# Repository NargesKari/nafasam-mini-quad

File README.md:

# nafasam-mini-quad

A phone-to-ESP32 wireless control link for a quadcopter, built around a hand-specified binary protocol with a checksum, a kill switch, and a failsafe — the network layer a drone project needs before the flight controller is worth writing.

## What it does

- Runs the ESP32 as an open WiFi access point (`nafasm`) serving a touch-control web page straight from flash, so any phone can connect with no app install.
- The page has two virtual joysticks (left: throttle/yaw, right: pitch/roll), an ARM/DISARM button, status lights (link / IMU / armed) and a help panel. It polls `GET /control` every 100 ms.
- A 200 Hz FreeRTOS task on core 0 reads the MPU6050 directly over its registers (no library), estimates roll/pitch with a complementary filter, runs PID stabilisation, mixes for an X-configuration quad and drives four transistor-switched brushed motors with PWM.
- Safety: failsafe disarm after 500 ms of silence, arm refused with throttle up, motors off on any IMU error, crash-angle disarm.

See `docs/protocol.md` for the exact contract.

## Repo layout

- `firmware/nafasam_quad/` - Arduino sketch (`.ino`, `config.h` pins/PID/safety, `mpu6050.*` driver, generated `web_page.h`)
- `web/public/index.html` - control page (single source of truth)
- `hardware/` - schematics, PCB, datasheets, mechanical parts
- `docs/` - protocol
- `scripts/generate_web_header.py` - embeds the page into the firmware

## Getting started

Arduino IDE with the ESP32 core v3.x (no extra libraries), open `firmware/nafasam_quad/nafasam_quad.ino`, select an ESP32 Dev Module, upload. Power the drone flat and still: the gyro calibrates at boot.

If you edit the control page:

```bash
python3 scripts/generate_web_header.py   # then re-flash
```

Connect to the `nafasm` WiFi and open `http://192.168.4.1/`.

**First power-up: remove the propellers** and check each motor's direction and the sign of the stabilisation on the bench before any flight.

<!-- add screenshot/demo here -->

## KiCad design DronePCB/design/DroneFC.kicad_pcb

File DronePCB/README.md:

# DroneFC — engineering prototype A0

Open **design/DroneFC.kicad_pro** in KiCad 10. The project includes an editable seven-page schematic, a four-layer PCB, and local symbol/footprint libraries. The local libraries make the project portable.

**This is a prototype design, not a flight-tested or production-qualified controller. Read reports/validation-summary.json for the latest checks. Do not fabricate from an intermediate routing file.**

## Design choices

- ESP32-S3-MINI-1-N4R2: soldered module with 4 MB flash and 2 MB PSRAM. The module integrates RF circuitry and a PCB antenna. A bare ESP32 silicon implementation would require additional RF, clock and memory design.
- MPU-6050 bare QFN chip, I2C address 0x68. The auxiliary sensor bus and reserved pins are intentionally unused.
- Four AO3400A low-side motor switches, four SS34 flyback diodes, 100-ohm gate resistors, and 10-kilohm gate-to-source pulldowns.
- One 700 mAh, 20C, 1S LiPo. The advertised continuous discharge calculation is 0.7 Ah × 20 = 14 A; it does not establish the battery's real internal resistance or transient capability.
- TPS63021 fixed 3.3 V buck-boost converter for electronics, with a 1.5 uH inductor, two 10 uF input capacitors, three 22 uF output capacitors, and 100 nF control-supply bypass. Target electronics load is up to 1 A at battery voltage ≥3.0 V, subject to thermal/transient testing.
- TLV70028 and TLV70012 regulators provide the camera's 2.8 V and 1.2 V rails.
- A 10-ohm/1 uF filter feeds the IMU; local VDD, VLOGIC, REGOUT and CPOUT capacitors are 100 nF, 10 nF, 100 nF and 2.2 nF respectively. CPOUT uses a 50 V-rated capacitor.
- No charging circuit, SD card slot, USB socket, development-board headers, or flash LED. Programming uses solder pads and an external 3.3 V UART adapter.

## Mechanical and stackup intent

PCB outline: **50 × 50 mm**, nominal **0.8 mm** FR4, four copper layers. This is the first layout size, not a claim of minimum achievable size or mass. The antenna end of the ESP32 module extends beyond the PCB outline, so the assembled envelope is larger than 50 mm in that direction.

Layers: front signals/components, inner ground, inner battery distribution, back signals. Two camera signals (PCLK and RESET) also use the battery layer with clearance around them; the ground plane remains continuous. Ground and battery use solid connections to the inner planes. The motor-current pads use multiple vias. The final copper thickness, stackup, minimum spacing and via process must be agreed with the board manufacturer. The thermal/current assumptions require approximately 35 um finished copper on the power planes and outer layers; do not silently substitute thinner inner copper.

U2 uses the local TI_DSJ14_TPS63021 footprint, with a 1.58 × 2.85 mm exposed ground pad checked against TI drawing 4208549-3/E. Its peripheral lands are slightly enlarged relative to TI's example. Segmented paste covers approximately 65% of the exposed pad. Have the assembler qualify stencil thickness and via-in-pad treatment, including the module ground pads and the regulator ground connection. This is not a qualified assembly process.

Four M2 clearance holes use a nominal 44 × 26 mm spacing. Confirm that this pattern fits the frame. Keep the module antenna free of battery, carbon fibre, motors and wiring. The PCB is a controller mounted to a frame, not a structural motor-support plate.

## Camera compatibility

J3 uses **Hirose FH12-24S-0.5SH(55)**, a 24-pin, 0.5 mm pitch, bottom-contact FPC connector. Its electrical pinout follows the OV2640 interface shown in the AI-Thinker ESP32-CAM v1.6 reference schematic archived in references/ESP32_CAM_V1.6.pdf.

Buy only a camera flex assembly with this exact pinout. “OV2640” alone does not specify the connector pinout, contact side, flex thickness, lens clearance or power rails. The final camera assembly has not been selected from a seller. **The seller's flex drawing must be checked before fabrication.** The provided connector is not a generic plug for every ESP32 camera.

The camera's Y2–Y9 lines form D0–D7. Y0/Y1 and pin24 are unused. Camera I/O runs at 3.3 V, analog at 2.8 V and core at 1.2 V, consistent with the referenced assembly. See pin-map.json for the exact connections.

## Motor and battery connections

J2 pin1 is battery positive, pin2 is ground. J4–J7 pin1 is motor positive (VBAT), pin2 is the switched motor negative. SS34 cathodes connect to VBAT and anodes to motor negative. AO3400A pin1 is gate, pin2 source, pin3 drain.

**C101–C104 are off-board components:** solder one 100 nF, 16 V ceramic directly across each motor's terminals. Their presence in the BOM is intentional; they have no PCB footprints. C25–C28 are separate local 10 uF rail-decoupling capacitors near the motor drivers. C11 is a low-ESR 220 uF bulk capacitor. Its exact manufacturer part number, ripple rating, ESR and height remain a sourcing check; its allocated package is 6.3 × 5.8 mm.

The linked ECA listing describes 1.74 A as maximum loaded current. Four motors at that figure draw 6.96 A, excluding electronics. Stall/startup current is not specified by that figure. Measure it with current limiting and appropriate test equipment. Do not infer MOSFET, diode or battery stall survival from their headline current ratings.

AO3400A's specified 48 milliohm maximum at 2.5 V gate drive gives approximately 0.145 W conduction loss per motor at 1.74 A and continuous on-time at the datasheet reference temperature. Hot resistance, switching loss and flyback-diode dissipation increase the actual thermal load. This calculation is not a thermal qualification.

There is no reverse-polarity protection, battery charger or hardware LiPo cutoff on this board. Confirm polarity before connection, use an external 1S charger, and disconnect the battery after use. Battery voltage monitoring is available to firmware through a 100k/100k divider and 100 nF filter. The nominal ADC scale factor is 2, with calibration still required.

## Programming and firmware requirements

J1 pads, in order: GND, 3V3, UART_TX, UART_RX, BOOT, ESP_EN. Use **3.3 V logic**. Connect adapter TX to board RX and adapter RX to board TX. With the battery powering the board, use J1's 3V3 as a reference only; do not connect a second driven supply. Hold BOOT low while pulsing ESP_EN low to enter the ROM loader.

The included firmware header only defines hardware pins. It is not flight-control firmware. Before flying, implement and test local IMU sampling, calibration, attitude estimation, motor mixing, arming, link-loss response, watchdog response and low-battery handling. Flight stabilization must run locally; Wi-Fi carries commands/video rather than providing the timing of the stabilization loop. Keep camera processing from delaying the control loop.

All motor PWM outputs must initialize low. Establish a measured control-loop budget with camera streaming enabled. A fresh 1S cell reaches 4.2 V; the motors are listed as nominal 3.7 V. Confirm their permitted supply and use a battery-aware duty limit as appropriate. An average-voltage duty limit does not limit instantaneous stall current.

## Bench acceptance before flight

1. Inspect soldering and check supply resistance and polarity without battery connected. Start on a current-limited supply with motors disconnected.
2. Sweep battery input over the intended operating range and verify 3.3 V, 2.8 V, 1.2 V and IMU supply voltage, including camera/Wi-Fi transients.
3. Read MPU-6050 identity, check stationary gyro/accelerometer readings and confirm axis orientation. Check camera frames and the UART boot process.
4. With propellers removed, verify each motor remains off at boot/reset and test PWM individually. Then use a restrained thrust test to establish propeller load, startup current, voltage sag and component temperature.
5. Verify arming, loss-of-link response, watchdog reset and low-battery behavior before any flight. Establish thrust margin using the actual all-up mass.

## Sources

- [ESP32-S3-MINI module datasheet](https://documentation.espressif.com/esp32-s3-mini-1_mini-1u_datasheet_en.html)
- [Espressif camera driver and supported sensors](https://github.com/espressif/esp32-camera)
- [AI-Thinker ESP32-CAM v1.6 reference schematic, hosted by Seeed](https://github.com/SeeedDocument/forum_doc/blob/master/reg/ESP32_CAM_V1.6.pdf)
- [MPU-6000/6050 manufacturer specification](https://invensense.tdk.com/wp-content/uploads/2015/02/MPU-6000-Datasheet.pdf)
- [AO3400A manufacturer specifications](https://www.aosmd.com/products/mosfets/low-voltage-mosfets-12v-30v/ao3400a)
- [TPS63020/21 manufacturer datasheet](https://www.ti.com/lit/ds/symlink/tps63020.pdf)
- [XFL4020 inductor drawing](https://www.coilcraft.com/getmedia/50632d43-da1b-4cdb-8ab4-3029cab51df3/xfl4020.pdf)
- [Hirose camera connector](https://www.hirose.com/product/p/CL0586-0521-0-55)
- [ECA 8520 motor listing](https://eshop.eca.ir/موتور-coreless/6933-موتور-coreless-سایز-8520.html)

## Project contents

- design/DroneFC.kicad_pro, .kicad_sch and .kicad_pcb: editable KiCad project.
- BOM.csv: individual component values, packages and sourcing notes.
- design_manifest.json: component/net design intent; the PCB contains the final adjusted placement.
- pin-map.json and drone_pins.h: interface mapping.
- reports/: electrical, physical and connectivity checks.
- preview/: schematic and board previews.
- tools/ (working directory only, omitted from the delivery archive): development helpers and project-local routing tools. These contain intermediate design assumptions. Re-running build_design.py with --pcb replaces the board with its initial unrouted placement. Preserve the final PCB and local libraries before regenerating.

## Validation and delivery

The final routed PCB passes the configured KiCad electrical and physical checks with zero reported violations and zero unconnected items. An independent exported-netlist comparison matches all 240 connected component pins between schematic and PCB. The JSON reports list the checks that KiCad ignores under the project settings; a clean report does not establish thermal performance, signal integrity or flight suitability.

DroneFC-prototype-A0.zip contains the editable design, local libraries, component list, pin mapping, final reports and previews. No manufacturing release is included: camera flex compatibility, C11 sourcing, assembly process and manufacturer stackup still require confirmation. Actual motor startup/stall current, rail transients, thermal behavior and thrust margin require hardware tests. Board mass and efficiency have not been measured.

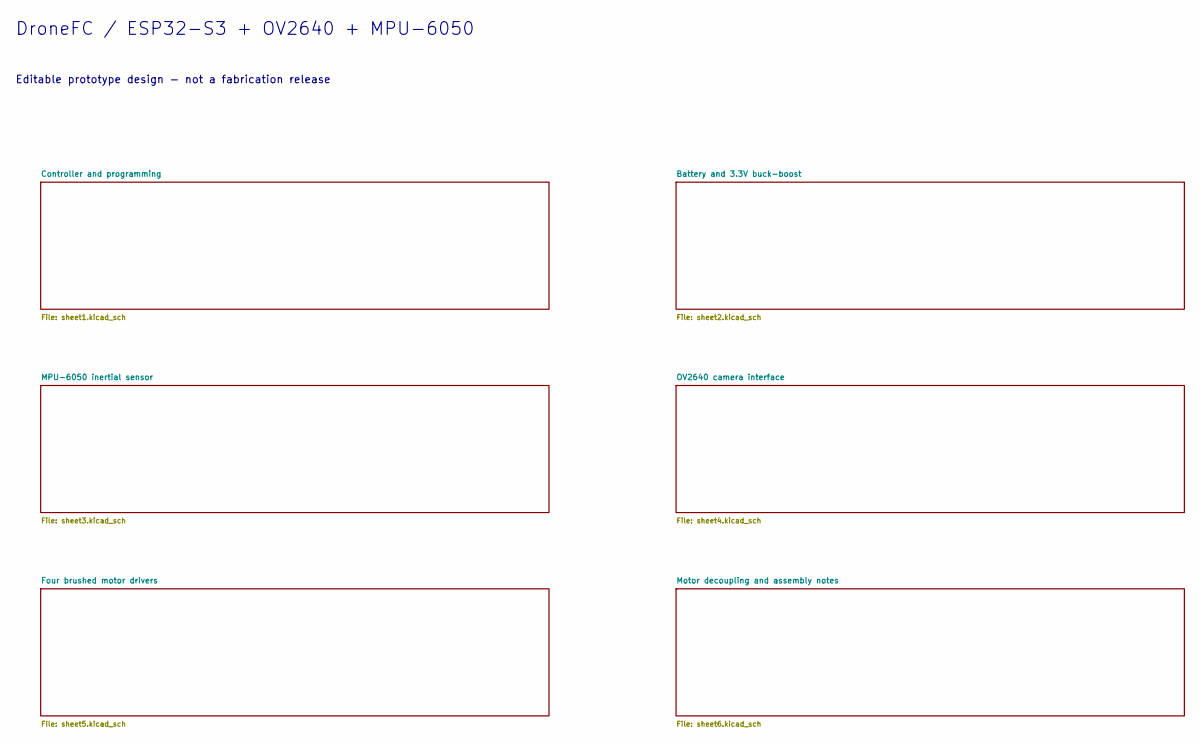
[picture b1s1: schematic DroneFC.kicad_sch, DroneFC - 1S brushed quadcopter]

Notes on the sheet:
DroneFC / ESP32-S3 + OV2640 + MPU-6050
Editable prototype design - not a fabrication release

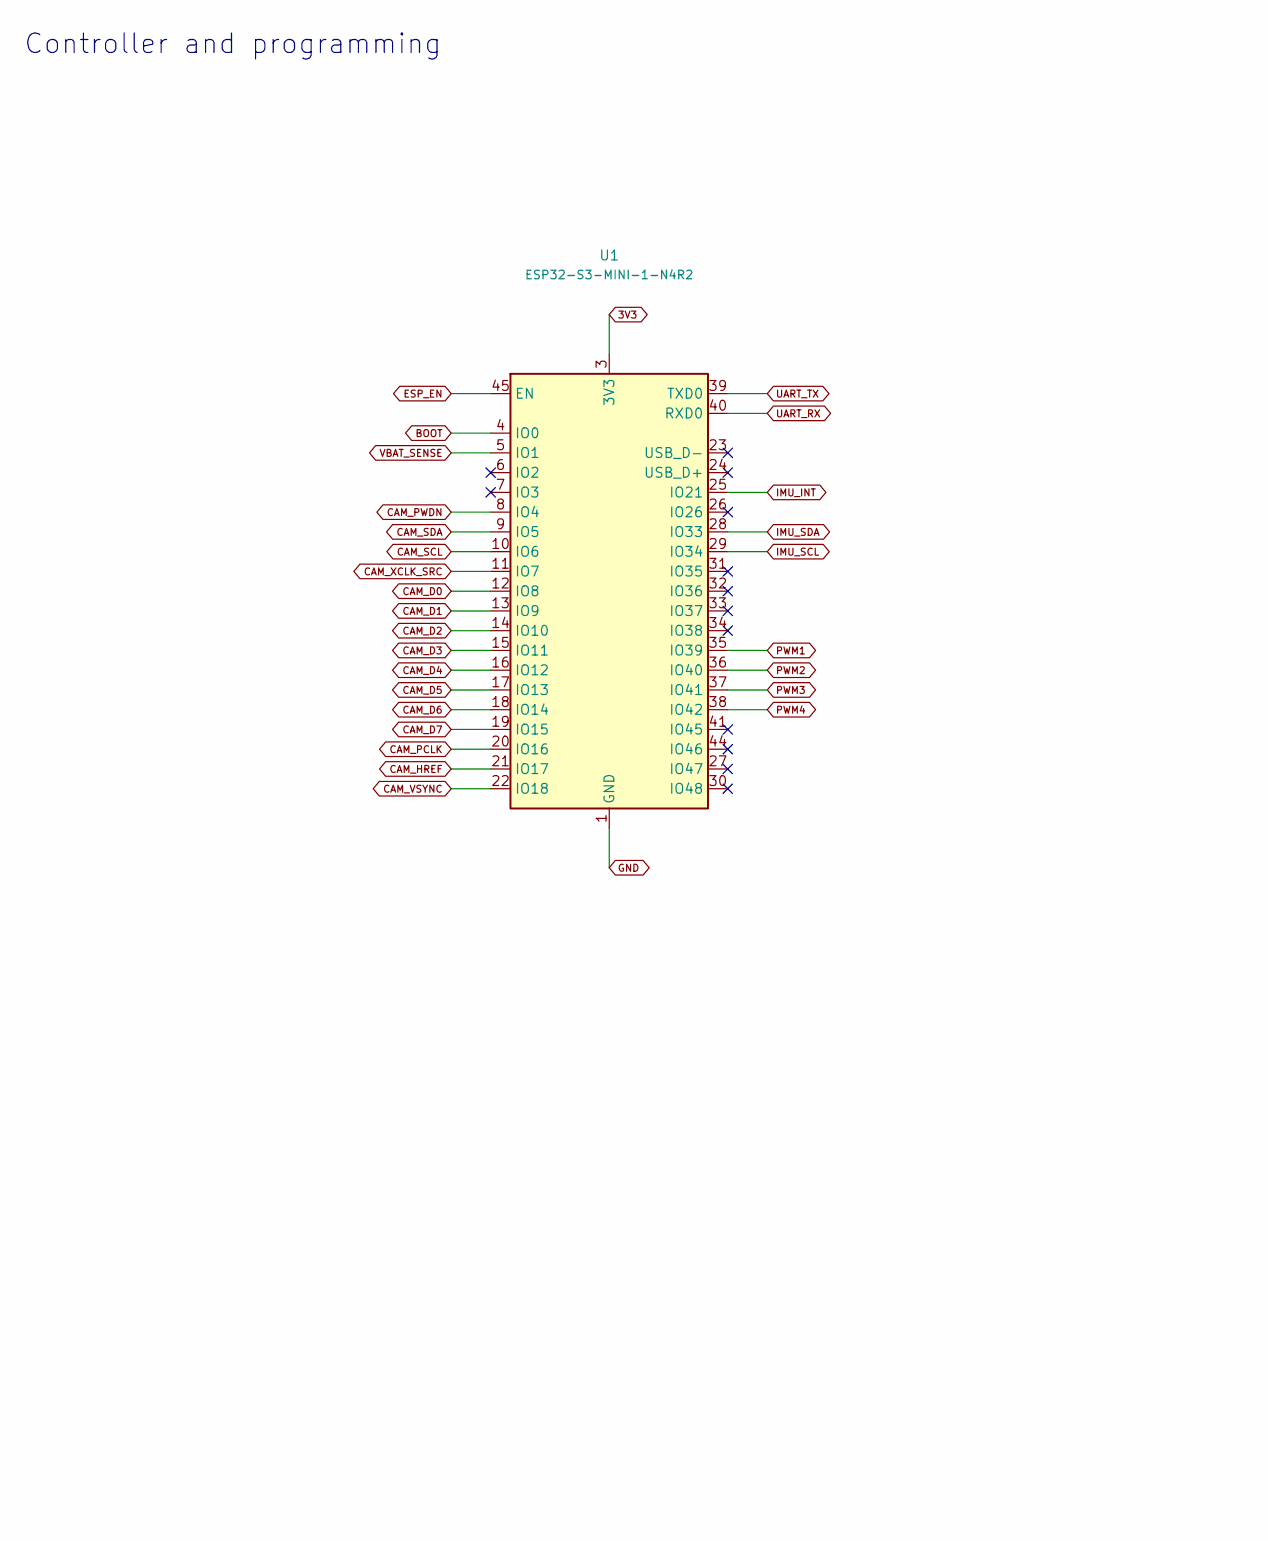
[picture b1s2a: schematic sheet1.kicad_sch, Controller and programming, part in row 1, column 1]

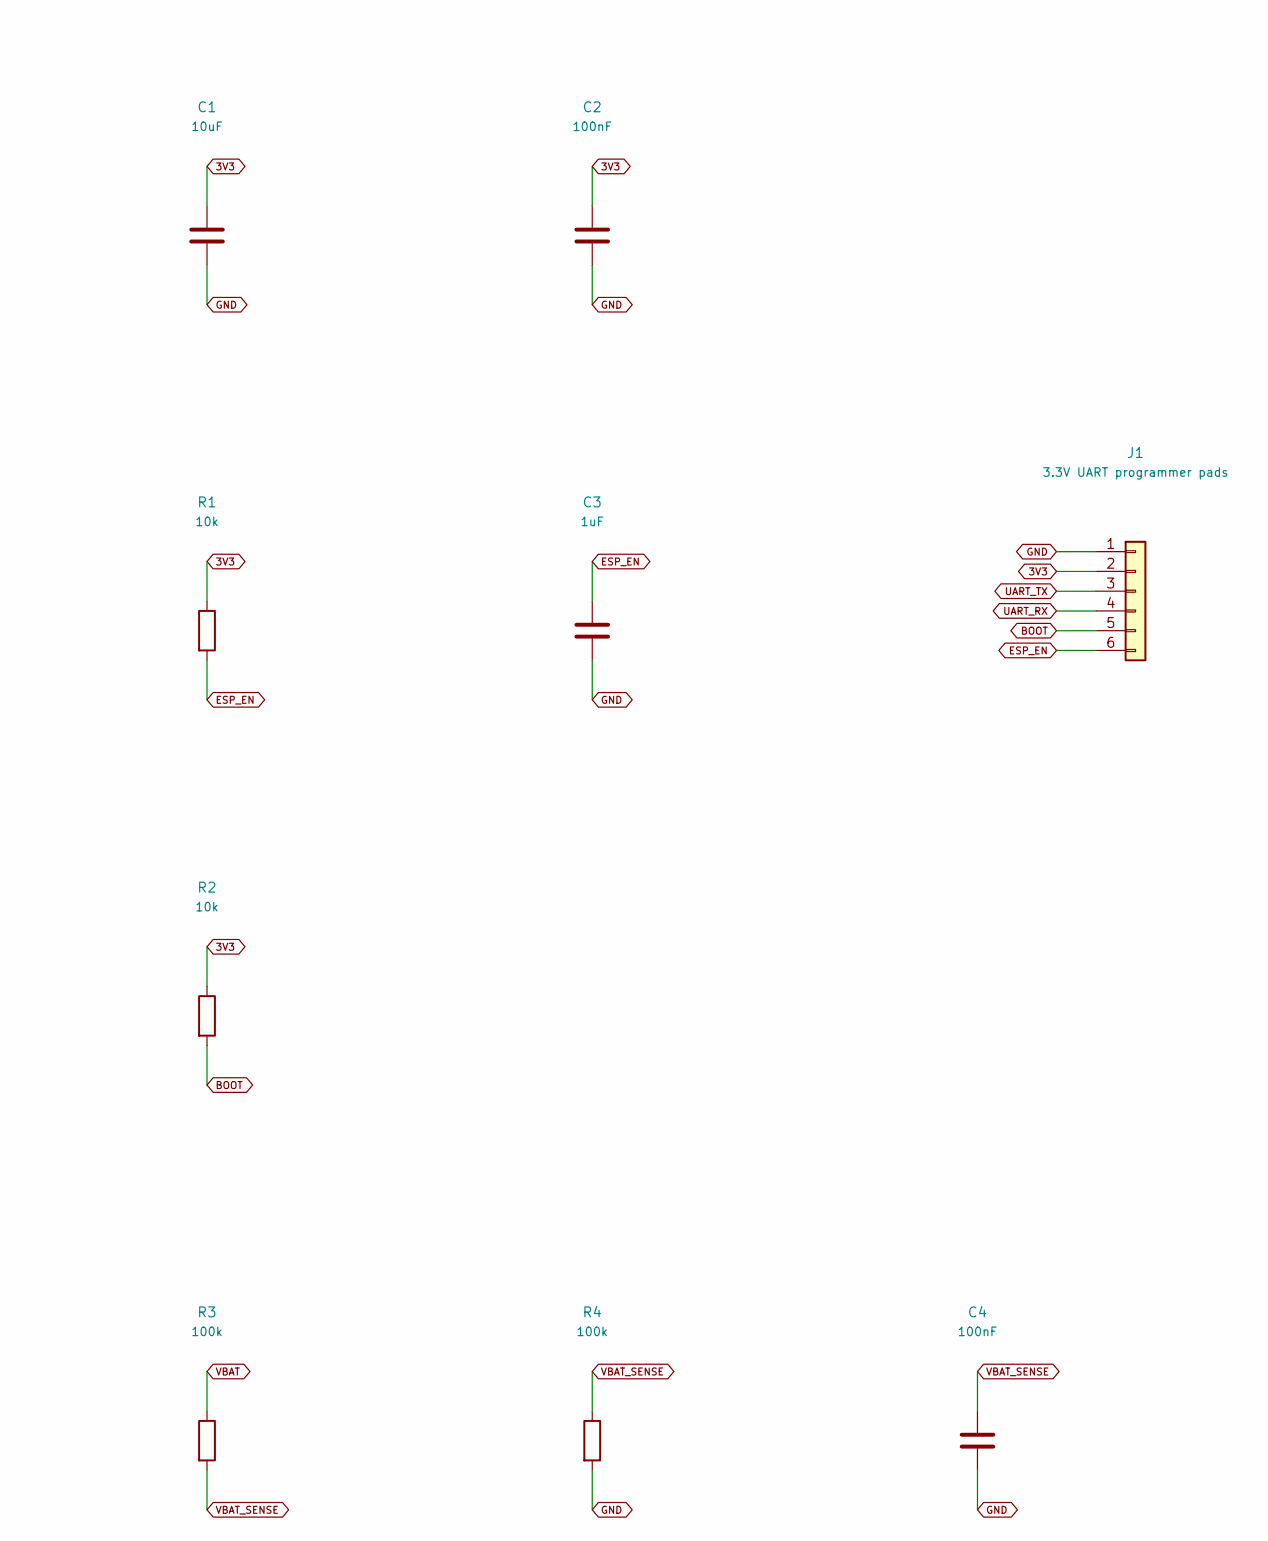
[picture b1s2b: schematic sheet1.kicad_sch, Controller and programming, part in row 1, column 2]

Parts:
C1: 10uF; C_0603_1608Metric
C2, C4: 100nF; C_0402_1005Metric
C3: 1uF; C_0402_1005Metric
J1: 3.3V UART programmer pads; Programming_6
R1, R2: 10k; R_0402_1005Metric
R3, R4: 100k; R_0402_1005Metric
U1: ESP32-S3-MINI-1-N4R2; ESP32-S2-MINI-1

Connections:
3V3: C1.1, C2.1, J1.2, R1.1, R2.1, U1.3 (3V3); also elsewhere on the board
BOOT: J1.5, R2.2, U1.4 (IO0)
CAM_D0: U1.12 (IO8); also elsewhere on the board
CAM_D1: U1.13 (IO9); also elsewhere on the board
CAM_D2: U1.14 (IO10); also elsewhere on the board
CAM_D3: U1.15 (IO11); also elsewhere on the board
CAM_D4: U1.16 (IO12); also elsewhere on the board
CAM_D5: U1.17 (IO13); also elsewhere on the board
CAM_D6: U1.18 (IO14); also elsewhere on the board
CAM_D7: U1.19 (IO15); also elsewhere on the board
CAM_HREF: U1.21 (IO17); also elsewhere on the board
CAM_PCLK: U1.20 (IO16); also elsewhere on the board
CAM_PWDN: U1.8 (IO4); also elsewhere on the board
CAM_SCL: U1.10 (IO6); also elsewhere on the board
CAM_SDA: U1.9 (IO5); also elsewhere on the board
CAM_VSYNC: U1.22 (IO18); also elsewhere on the board
CAM_XCLK_SRC: U1.11 (IO7); also elsewhere on the board
ESP_EN: C3.1, J1.6, R1.2, U1.45 (EN)
GND: C1.2, C2.2, C3.2, C4.2, J1.1, R4.2, U1.1 (GND), U1.2 (GND), U1.42 (GND), U1.43 (GND), U1.46 (GND), U1.47 (GND), U1.48 (GND), U1.49 (GND), U1.50 (GND), U1.51 (GND), U1.52 (GND), U1.53 (GND), U1.54 (GND), U1.55 (GND), U1.56 (GND), U1.57 (GND), U1.58 (GND), U1.59 (GND), U1.60 (GND), U1.61 (GND), U1.62 (GND), U1.63 (GND), U1.64 (GND), U1.65 (GND); also elsewhere on the board
IMU_INT: U1.25 (IO21); also elsewhere on the board
IMU_SCL: U1.29 (IO34); also elsewhere on the board
IMU_SDA: U1.28 (IO33); also elsewhere on the board
PWM1: U1.35 (IO39); also elsewhere on the board
PWM2: U1.36 (IO40); also elsewhere on the board
PWM3: U1.37 (IO41); also elsewhere on the board
PWM4: U1.38 (IO42); also elsewhere on the board
UART_RX: J1.4, U1.40 (RXD0)
UART_TX: J1.3, U1.39 (TXD0)
VBAT: R3.1; also elsewhere on the board
VBAT_SENSE: C4.1, R3.2, R4.1, U1.5 (IO1)

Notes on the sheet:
Controller and programming

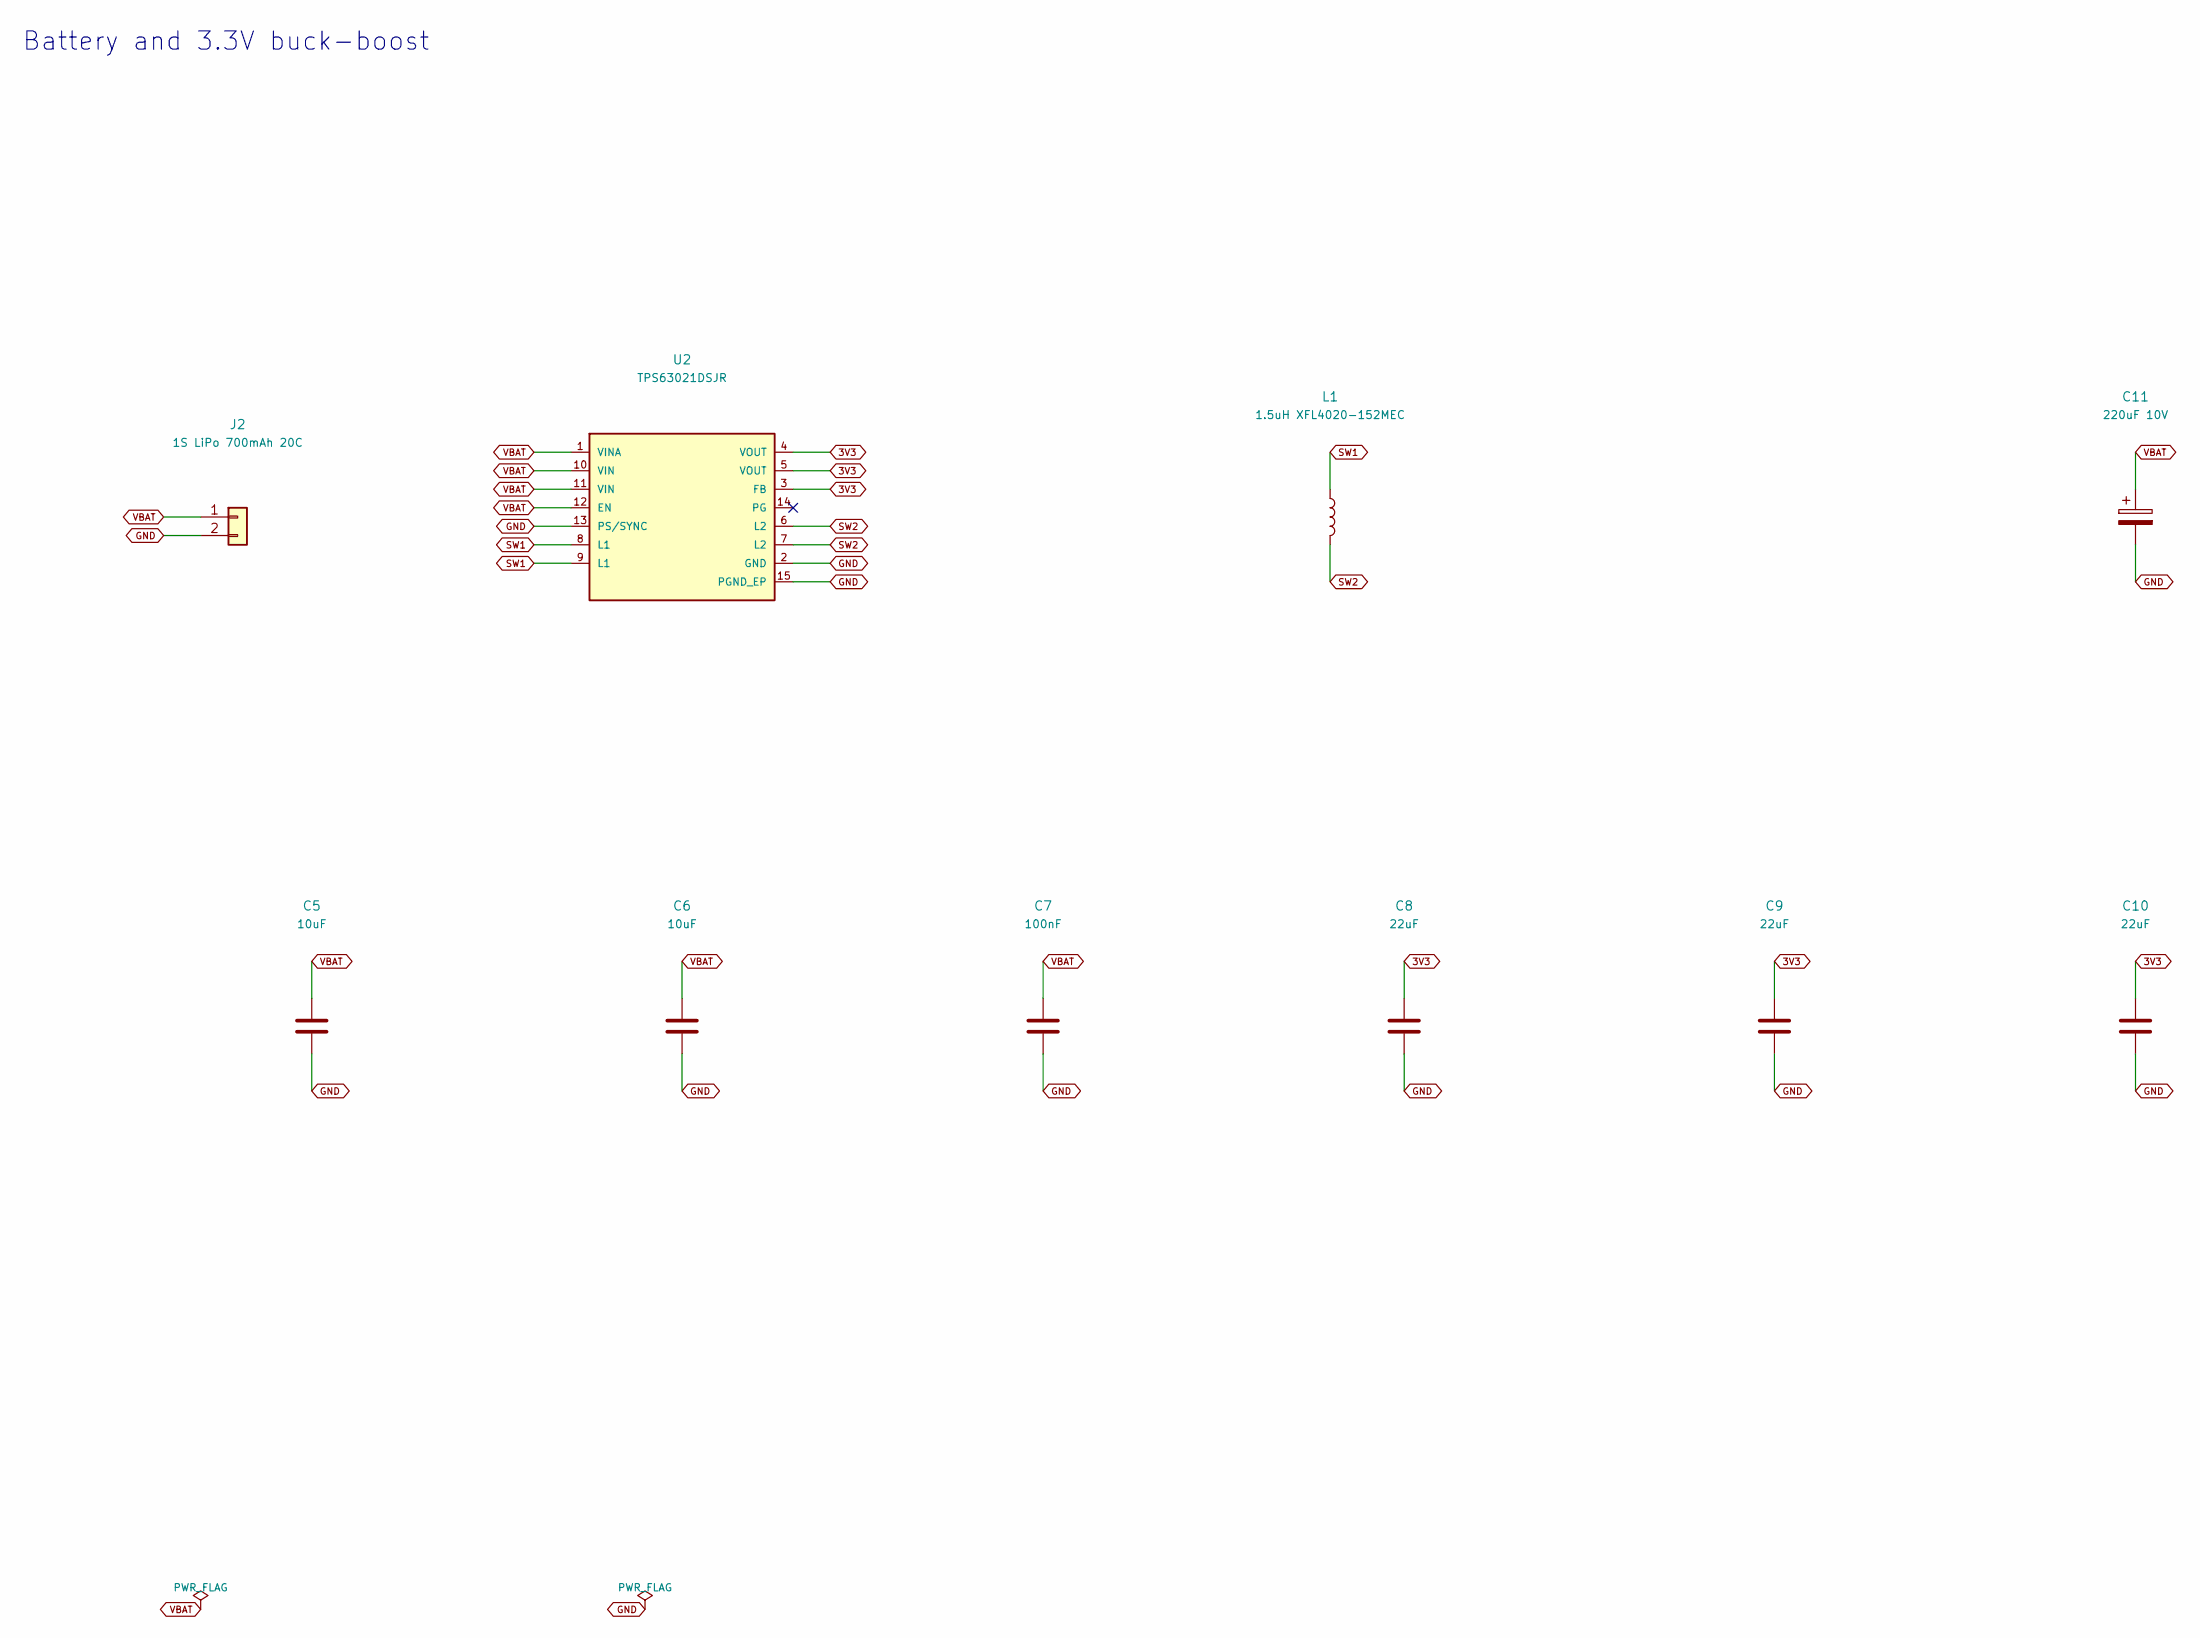
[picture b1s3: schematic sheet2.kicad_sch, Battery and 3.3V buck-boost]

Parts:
C5, C6: 10uF; C_0603_1608Metric
C7: 100nF; C_0402_1005Metric
C8, C9, C10: 22uF; C_0805_2012Metric
C11: 220uF 10V; CP_Elec_6.3x5.8
J2: 1S LiPo 700mAh 20C; Battery_2
L1: 1.5uH XFL4020-152MEC; XFL4020
U2: TPS63021DSJR; TI_DSJ14_TPS63021

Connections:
3V3: C8.1, C9.1, C10.1, U2.3 (FB), U2.4 (VOUT), U2.5 (VOUT); also elsewhere on the board
GND: C5.2, C6.2, C7.2, C8.2, C9.2, C10.2, C11.2, J2.2, U2.2 (GND), U2.13 (PS/SYNC), U2.15 (PGND_EP); also elsewhere on the board
SW1: L1.1, U2.8 (L1), U2.9 (L1)
SW2: L1.2, U2.6 (L2), U2.7 (L2)
VBAT: C5.1, C6.1, C7.1, C11.1, J2.1, U2.1 (VINA), U2.10 (VIN), U2.11 (VIN), U2.12 (EN); also elsewhere on the board

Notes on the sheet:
Battery and 3.3V buck-boost

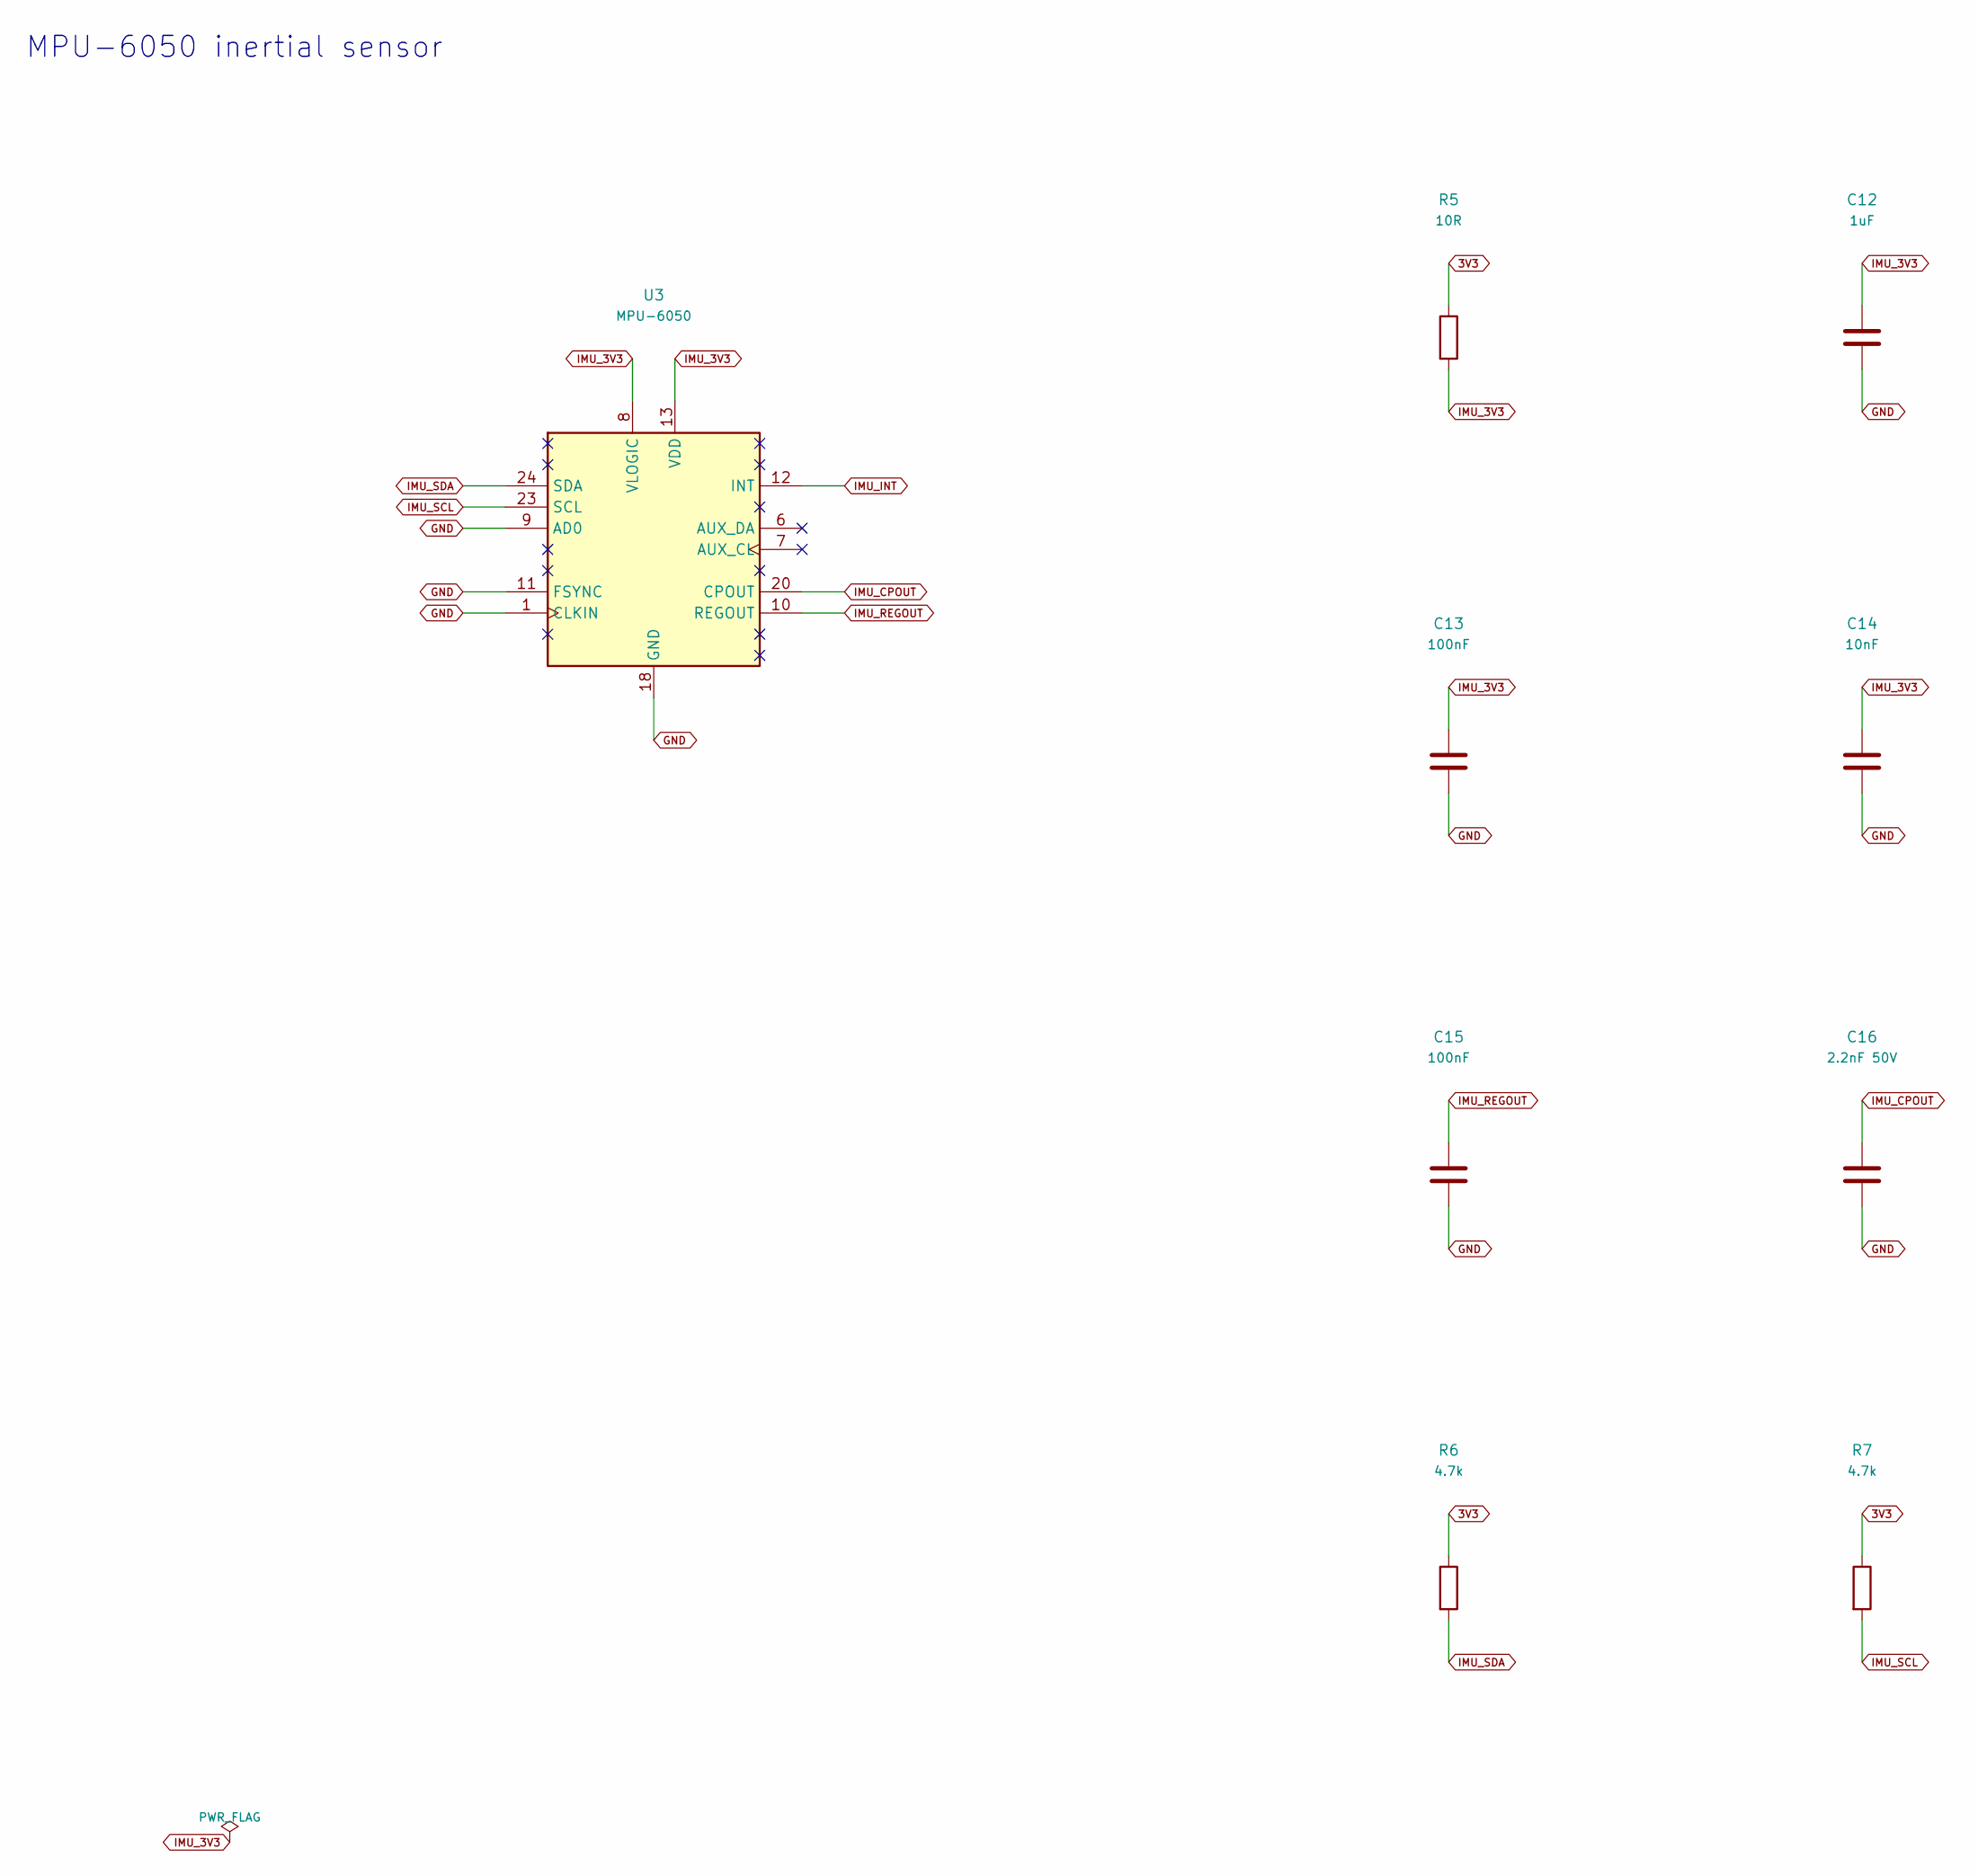
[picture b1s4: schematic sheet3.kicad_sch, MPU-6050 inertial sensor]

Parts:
C12: 1uF; C_0402_1005Metric
C13, C15: 100nF; C_0402_1005Metric
C14: 10nF; C_0402_1005Metric
C16: 2.2nF 50V; C_0402_1005Metric
R5: 10R; R_0402_1005Metric
R6, R7: 4.7k; R_0402_1005Metric
U3: MPU-6050; InvenSense_QFN-24_4x4mm_P0.5mm

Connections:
3V3: R5.1, R6.1, R7.1; also elsewhere on the board
GND: C12.2, C13.2, C14.2, C15.2, C16.2, U3.1 (CLKIN), U3.9 (AD0), U3.11 (FSYNC), U3.18 (GND); also elsewhere on the board
IMU_3V3: C12.1, C13.1, C14.1, R5.2, U3.8 (VLOGIC), U3.13 (VDD)
IMU_CPOUT: C16.1, U3.20 (CPOUT)
IMU_INT: U3.12 (INT); also elsewhere on the board
IMU_REGOUT: C15.1, U3.10 (REGOUT)
IMU_SCL: R7.2, U3.23 (SCL); also elsewhere on the board
IMU_SDA: R6.2, U3.24 (SDA); also elsewhere on the board

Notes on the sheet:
MPU-6050 inertial sensor

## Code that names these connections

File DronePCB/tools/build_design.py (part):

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r('R1','10k','3V3','ESP_EN',1,195,95,136,102,90)
c('C3','1uF','ESP_EN',1,245,95,136,104,90)
r('R2','10k','3V3','BOOT',1,195,145,115,109,90)
add('J1',CON6,'3.3V UART programmer pads',{1:'GND',2:'3V3',3:'UART_TX',4:'UART_RX',5:'BOOT',6:'ESP_EN'},1,315,90,141,108,fp='Drone:Programming_6',note='External programmer: 3.3V logic only; pin2 reference only with battery attached')
r('R3','100k','VBAT','VBAT_SENSE',1,195,200,112,119,90)
r('R4','100k','VBAT_SENSE','GND',1,245,200,114,119,90)
c('C4','100nF','VBAT_SENSE',1,295,200,116,119,90)
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r('R10','10k','3V3','CAM_RESET',4,315,200,135,130,90)
c('C24','100nF','CAM_RESET',4,65,250,137,130,90)
r('R11','10k','CAM_PWDN','GND',4,150,250,129,132,90)
r('R12','33R','CAM_XCLK_SRC','CAM_XCLK',4,240,250,115,114,90,note='Source series damping; tune with scope')

# Four low-side brushed motor drivers. Diode cathode to VBAT, anode to drain.
for i,(px,py) in enumerate([(106,113),(144,113),(106,143),(144,143)],1):
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
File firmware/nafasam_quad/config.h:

#pragma once
#include <Arduino.h>

// ============================================================================
// Nafasam Mini Quad - Configuration & Hardware Pin Mapping
// Original PCB target: ESP32-S3-MINI-1-N4R2, DroneFC PCB Revision A0
// Pin map below is CUSTOMISED: motors 23/22/35/34, IMU 18/19/21
// Coreless Brushed Motors: 8520 (3.7V nominal, 1S LiPo)
// IMU: InvenSense MPU-6050 (QFN-24 bare chip on I2C address 0x68)
// ============================================================================

// ---------------- WiFi Access Point ----------------
#define AP_SSID             "Nafasam"
#define AP_PASSWORD         ""             // Empty = open network; otherwise 8+ chars
#define AP_CHANNEL          1
#define AP_MAX_CONN         4

// ---------------- I2C & IMU (MPU-6050) ----------------
// Custom wiring: IMU_SDA -> GPIO 18, IMU_SCL -> GPIO 19, IMU_INT -> GPIO 21
#define PIN_I2C_SDA         18
#define PIN_I2C_SCL         19
#define PIN_IMU_INT         21             // IMU INT (defined, not used by the firmware)
#define DRONE_IMU_I2C_ADDR  0x68           // MPU-6050 address
#define I2C_FREQ_HZ         400000         // 400 kHz Fast Mode
#define I2C_TIMEOUT_MS      10

// ---------------- Motors (8520 Brushed Coreless) ----------------
// Low-side AO3400A MOSFET switches on DroneFC PCB:
// Motor 1 (J4): Front-Left  (FL) - Clockwise (CW)          -> GPIO 23 (PWM1)
// Motor 2 (J5): Front-Right (FR) - Counter-Clockwise (CCW) -> GPIO 22 (PWM2)
// Motor 3 (J6): Rear-Left   (RL) - Counter-Clockwise (CCW) -> GPIO 35 (PWM3)
// Motor 4 (J7): Rear-Right  (RR) - Clockwise (CW)          -> GPIO 34 (PWM4)
//
// NOTE: on the classic ESP32, GPIO 34..39 are INPUT-ONLY (no PWM/output), and on
// the ESP32-S3 GPIO 22..25 do not exist. The firmware checks this at boot and
// refuses to arm if a motor pin cannot drive an output.
#define PIN_MOTOR_FL        23             // Motor 1 (J4)
#define PIN_MOTOR_FR        22             // Motor 2 (J5)
#define PIN_MOTOR_RL        35             // Motor 3 (J6)
#define PIN_MOTOR_RR        34             // Motor 4 (J7)

// ---------------- Motor PWM Settings ----------------
// High frequency PWM (16 kHz) eliminates audible coil whine and drives 8520 motors efficiently
#define PWM_FREQ_HZ         16000
#define PWM_RES_BITS        10             // 10-bit resolution (0..1023)
#define PWM_MAX_DUTY        ((1 << PWM_RES_BITS) - 1)
#define MOTOR_MAX_THROTTLE  0.95f          // 95% ceiling for voltage/thermal safety margin

// ---------------- Battery Monitoring ----------------
// DroneFC PCB: VBAT_SENSE on GPIO 1 through 100k / 100k voltage divider (2:1 ratio)
#define PIN_BATTERY_ADC     1
#define BATTERY_DIVIDER_RATIO 2.0f
#define BATTERY_LOW_VOLTS   3.30f          // Low battery warning threshold
#define BATTERY_CRIT_VOLTS  3.10f          // Critical battery threshold

// ---------------- Flight Loop (Core 0 FreeRTOS Task) ----------------
#define LOOP_PERIOD_MS      5              // 200 Hz control loop (5 ms)
#define FLIGHT_TASK_CORE    0
#define FLIGHT_TASK_PRIO    10
#define FLIGHT_TASK_STACK   8192

#define COMPLEMENTARY_ALPHA 0.98f          // Gyro weight in complementary filter
#define MAX_TILT_DEG        25.0f          // Full stick = 25 degrees tilt
#define MAX_YAW_RATE_DPS    150.0f         // Full stick = 150 deg/s yaw rate
#define CRASH_ANGLE_DEG     65.0f          // Tilt past this threshold triggers emergency disarm

// ---------------- PID Stabilisation Tuning ----------------
#define KP_ANGLE            0.014f         // Proportional gain per degree of error
#define KI_ANGLE            0.008f         // Integral gain per degree-second
#define KD_ANGLE            0.0020f        // Derivative gain per deg/s of gyro angular rate
#define I_LIMIT             0.08f          // Anti-windup limit for angle integral
#define KP_YAW_RATE         0.003f         // Proportional gain per deg/s of yaw rate error
#define PID_OUT_LIMIT       0.35f          // Max mixer contribution for roll/pitch PID
#define YAW_OUT_LIMIT       0.20f          // Max mixer contribution for yaw PID

// ---------------- Safety & Failsafes ----------------
#define FAILSAFE_MS         500            // Disarm after 500 ms of command silence
#define THROTTLE_DEADBAND   3              // Throttle % below which motors stay idle/off
#define ARM_MAX_THROTTLE    5              // Refuse arming if throttle exceeds 5%
#define IMU_FAIL_LIMIT      5              // Consecutive IMU read failures before failsafe
#define IMU_RETRY_MS        500            // IMU reconnection retry period
